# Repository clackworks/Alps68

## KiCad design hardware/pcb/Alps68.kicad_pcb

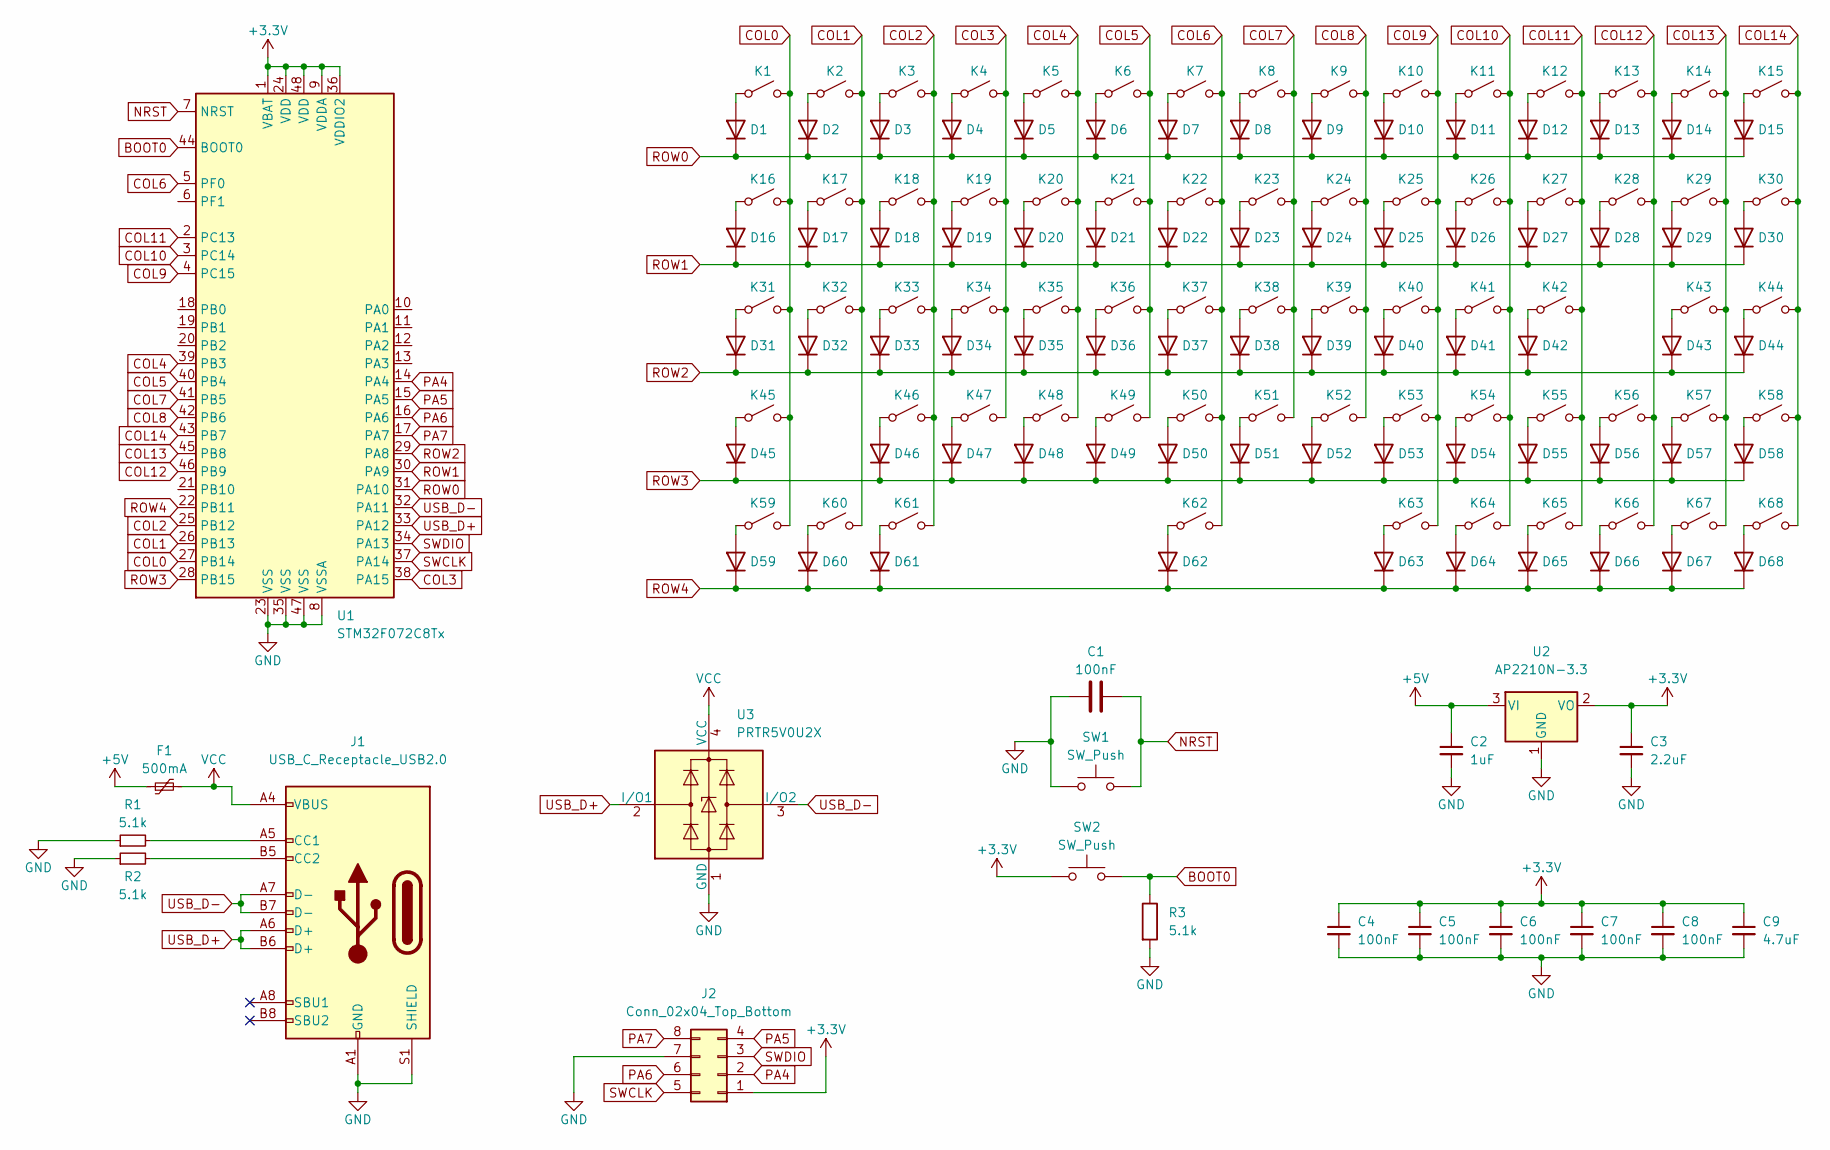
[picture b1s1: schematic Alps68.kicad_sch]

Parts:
C1, C4, C5, C6, C7, C8: 100nF; C_0805_2012Metric
C2: 1uF; C_0805_2012Metric
C3: 2.2uF; C_0805_2012Metric
C9: 4.7uF; C_0805_2012Metric
D1, D2, D3, D4, D5, D6, D7, D8, D9, D10, D11, D12, D13, D14, D15, D16, D17, D18, D19, D20, D21, D22, D23, D24, D25, D26, D27, D28, D29, D30, D31, D32, D33, D34, D35, D36, D37, D38, D39, D40, D41, D42, D43, D44, D45, D46, D47, D48, D49, D50, D51, D52, D53, D54, D55, D56, D57, D58, D59, D60, D61, D62, D63, D64, D65, D66, D67, D68: D; D_SOD-323_HandSoldering_NoSilkScreen
F1: 500mA; Fuse_0805_2012Metric
J1: USB_C_Receptacle_USB2.0; USB_C_Receptacle_HRO_TYPE-C-31-M-12
J2: Conn_02x04_Top_Bottom; PinHeader_2x04_P2.54mm_Vertical
K1, K2, K3, K4, K5, K6, K7, K8, K9, K10, K11, K12, K13, K15, K17, K18, K19, K20, K21, K22, K23, K24, K25, K26, K27, K28, K30, K32, K33, K34, K35, K36, K37, K38, K39, K40, K41, K42, K44, K46, K47, K48, K49, K50, K51, K52, K53, K54, K55, K57, K58, K63, K64, K65, K66, K67, K68: MX_Alps_Hybrid; MX-1U-NoLED
K14: MX_Alps_Hybrid; MX-2U-NoLED
K16, K29: MX_Alps_Hybrid; MX-1.5U-NoLED
K31, K56: MX_Alps_Hybrid; MX-1.75U-NoLED
K43, K45: MX_Alps_Hybrid; MX-2.25U-NoLED
K59, K60, K61: MX_Alps_Hybrid; MX-1.25U-NoLED
K62: MX_Alps_Hybrid; MX-6.25U-ReversedStabilizers-NoLED
R1, R2, R3: 5.1k; R_0805_2012Metric
SW1, SW2: SW_Push; SW_SPST_TS-1177
U1: STM32F072C8Tx; LQFP-48_7x7mm_P0.5mm
U2: AP2210N-3.3; SOT-23
U3: PRTR5V0U2X; SOT-143

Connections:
+3V3: C3.1, C4.1, C5.1, C6.1, C7.1, C8.1, C9.1, J2.1, SW2.1, U1.1 (VBAT), U1.9 (VDDA), U1.24 (VDD), U1.36 (VDDIO2), U1.48 (VDD), U2.2 (VO); also elsewhere on the board
+5V: C2.1, F1.1, U2.3 (VI)
BOOT0: R3.1, SW2.2, U1.44 (BOOT0); also elsewhere on the board
COL0: K1.1 (A), K16.1 (A), K31.1 (A), K45.1 (A), K59.1 (A), U1.27 (PB14)
COL1: K2.1 (A), K17.1 (A), K32.1 (A), K60.1 (A), U1.26 (PB13)
COL2: K3.1 (A), K18.1 (A), K33.1 (A), K46.1 (A), K61.1 (A), U1.25 (PB12)
COL3: K4.1 (A), K19.1 (A), K34.1 (A), K47.1 (A), U1.38 (PA15)
COL4: K5.1 (A), K20.1 (A), K35.1 (A), K48.1 (A), U1.39 (PB3)
COL5: K6.1 (A), K21.1 (A), K36.1 (A), K49.1 (A), U1.40 (PB4)
COL6: K7.1 (A), K22.1 (A), K37.1 (A), K50.1 (A), K62.1 (A), U1.5 (PF0)
COL7: K8.1 (A), K23.1 (A), K38.1 (A), K51.1 (A), U1.41 (PB5)
COL8: K9.1 (A), K24.1 (A), K39.1 (A), K52.1 (A), U1.42 (PB6)
COL9: K10.1 (A), K25.1 (A), K40.1 (A), K53.1 (A), K63.1 (A), U1.4 (PC15)
COL10: K11.1 (A), K26.1 (A), K41.1 (A), K54.1 (A), K64.1 (A), U1.3 (PC14)
COL11: K12.1 (A), K27.1 (A), K42.1 (A), K55.1 (A), K65.1 (A), U1.2 (PC13)
COL12: K13.1 (A), K28.1 (A), K56.1 (A), K66.1 (A), U1.46 (PB9)
COL13: K14.1 (A), K29.1 (A), K43.1 (A), K57.1 (A), K67.1 (A), U1.45 (PB8)
COL14: K15.1 (A), K30.1 (A), K44.1 (A), K58.1 (A), K68.1 (A), U1.43 (PB7)
GND: C1.1, C2.2, C3.2, C4.2, C5.2, C6.2, C7.2, C8.2, C9.2, J1.A1 (GND), J1.A12 (GND), J1.B1 (GND), J1.B12 (GND), J1.S1 (SHIELD), J2.7, R1.1, R2.1, R3.2, SW1.1, U1.8 (VSSA), U1.23 (VSS), U1.35 (VSS), U1.47 (VSS), U2.1 (GND), U3.1 (GND); also elsewhere on the board
NRST: C1.2, SW1.2, U1.7 (NRST); also elsewhere on the board
unnamed: D1.2 (A), K1.2 (B)
unnamed: D2.2 (A), K2.2 (B)
unnamed: D3.2 (A), K3.2 (B)
unnamed: D4.2 (A), K4.2 (B)
unnamed: D5.2 (A), K5.2 (B)
unnamed: D6.2 (A), K6.2 (B)
unnamed: D7.2 (A), K7.2 (B)
unnamed: D8.2 (A), K8.2 (B)
unnamed: D9.2 (A), K9.2 (B)
unnamed: D10.2 (A), K10.2 (B)
unnamed: D11.2 (A), K11.2 (B)
unnamed: D12.2 (A), K12.2 (B)
unnamed: D13.2 (A), K13.2 (B)
unnamed: D14.2 (A), K14.2 (B)
unnamed: D15.2 (A), K15.2 (B)
unnamed: D16.2 (A), K16.2 (B)
unnamed: D17.2 (A), K17.2 (B)
unnamed: D18.2 (A), K18.2 (B)
unnamed: D19.2 (A), K19.2 (B)
unnamed: D20.2 (A), K20.2 (B)
unnamed: D21.2 (A), K21.2 (B)
unnamed: D22.2 (A), K22.2 (B)
unnamed: D23.2 (A), K23.2 (B)
unnamed: D24.2 (A), K24.2 (B)
unnamed: D25.2 (A), K25.2 (B)
unnamed: D26.2 (A), K26.2 (B)
unnamed: D27.2 (A), K27.2 (B)
unnamed: D28.2 (A), K28.2 (B)
unnamed: D29.2 (A), K29.2 (B)
unnamed: D30.2 (A), K30.2 (B)
unnamed: D31.2 (A), K31.2 (B)
unnamed: D32.2 (A), K32.2 (B)
unnamed: D33.2 (A), K33.2 (B)
unnamed: D34.2 (A), K34.2 (B)
unnamed: D35.2 (A), K35.2 (B)
unnamed: D36.2 (A), K36.2 (B)
unnamed: D37.2 (A), K37.2 (B)
unnamed: D38.2 (A), K38.2 (B)
unnamed: D39.2 (A), K39.2 (B)
unnamed: D40.2 (A), K40.2 (B)
unnamed: D41.2 (A), K41.2 (B)
unnamed: D42.2 (A), K42.2 (B)
unnamed: D43.2 (A), K43.2 (B)
unnamed: D44.2 (A), K44.2 (B)
unnamed: D45.2 (A), K45.2 (B)
unnamed: D46.2 (A), K46.2 (B)
unnamed: D47.2 (A), K47.2 (B)
unnamed: D48.2 (A), K48.2 (B)
unnamed: D49.2 (A), K49.2 (B)
unnamed: D50.2 (A), K50.2 (B)
unnamed: D51.2 (A), K51.2 (B)
unnamed: D52.2 (A), K52.2 (B)
unnamed: D53.2 (A), K53.2 (B)
unnamed: D54.2 (A), K54.2 (B)
unnamed: D55.2 (A), K55.2 (B)
unnamed: D56.2 (A), K56.2 (B)
unnamed: D57.2 (A), K57.2 (B)
unnamed: D58.2 (A), K58.2 (B)
unnamed: D59.2 (A), K59.2 (B)
unnamed: D60.2 (A), K60.2 (B)
unnamed: D61.2 (A), K61.2 (B)
unnamed: D62.2 (A), K62.2 (B)
unnamed: D63.2 (A), K63.2 (B)
unnamed: D64.2 (A), K64.2 (B)
unnamed: D65.2 (A), K65.2 (B)
unnamed: D66.2 (A), K66.2 (B)
unnamed: D67.2 (A), K67.2 (B)
unnamed: D68.2 (A), K68.2 (B)
unnamed: J1.A5 (CC1), R1.2
unnamed: J1.B5 (CC2), R2.2
PA4: J2.2, U1.14 (PA4)
PA5: J2.4, U1.15 (PA5)
PA6: J2.6, U1.16 (PA6)
PA7: J2.8, U1.17 (PA7)
ROW0: D1.1 (K), D2.1 (K), D3.1 (K), D4.1 (K), D5.1 (K), D6.1 (K), D7.1 (K), D8.1 (K), D9.1 (K), D10.1 (K), D11.1 (K), D12.1 (K), D13.1 (K), D14.1 (K), D15.1 (K), U1.31 (PA10)
ROW1: D16.1 (K), D17.1 (K), D18.1 (K), D19.1 (K), D20.1 (K), D21.1 (K), D22.1 (K), D23.1 (K), D24.1 (K), D25.1 (K), D26.1 (K), D27.1 (K), D28.1 (K), D29.1 (K), D30.1 (K), U1.30 (PA9)
ROW2: D31.1 (K), D32.1 (K), D33.1 (K), D34.1 (K), D35.1 (K), D36.1 (K), D37.1 (K), D38.1 (K), D39.1 (K), D40.1 (K), D41.1 (K), D42.1 (K), D43.1 (K), D44.1 (K), U1.29 (PA8)
ROW3: D45.1 (K), D46.1 (K), D47.1 (K), D48.1 (K), D49.1 (K), D50.1 (K), D51.1 (K), D52.1 (K), D53.1 (K), D54.1 (K), D55.1 (K), D56.1 (K), D57.1 (K), D58.1 (K), U1.28 (PB15)
ROW4: D59.1 (K), D60.1 (K), D61.1 (K), D62.1 (K), D63.1 (K), D64.1 (K), D65.1 (K), D66.1 (K), D67.1 (K), D68.1 (K), U1.22 (PB11)
SWCLK: J2.5, U1.37 (PA14)
SWDIO: J2.3, U1.34 (PA13)
USB_D+: J1.A6 (D+), J1.B6 (D+), U1.33 (PA12), U3.2 (I/O1)
USB_D-: J1.A7 (D-), J1.B7 (D-), U1.32 (PA11), U3.3 (I/O2)
VCC: F1.2, J1.A4 (VBUS), J1.A9 (VBUS), J1.B4 (VBUS), J1.B9 (VBUS), U3.4 (VCC)

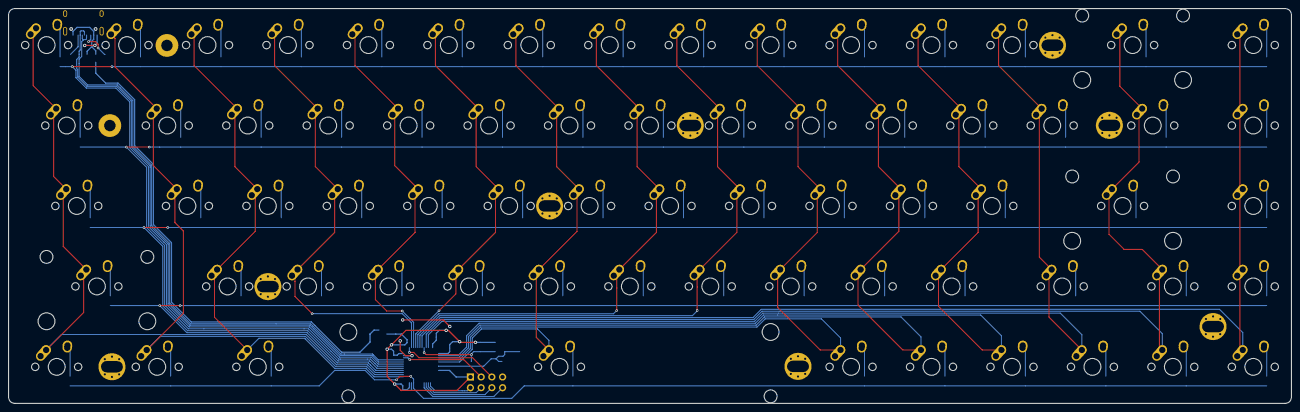
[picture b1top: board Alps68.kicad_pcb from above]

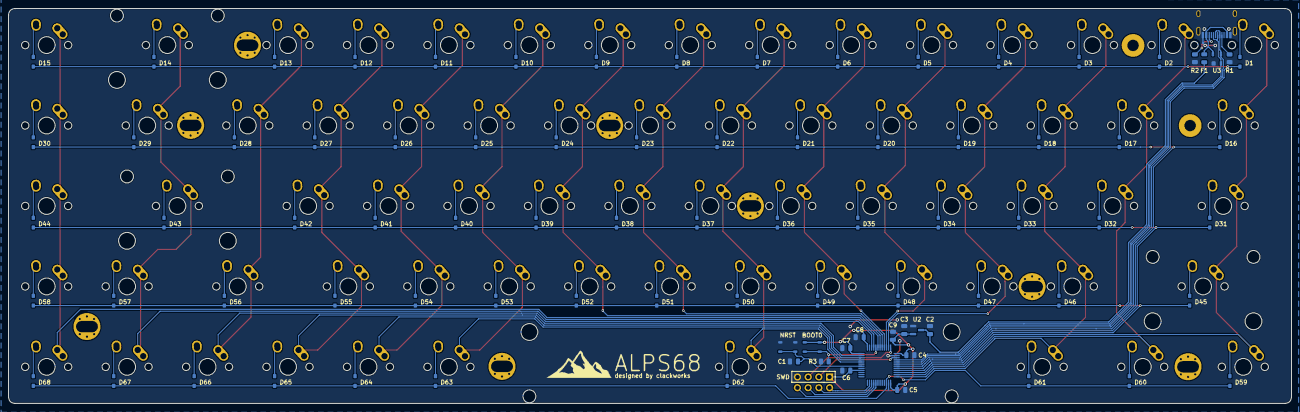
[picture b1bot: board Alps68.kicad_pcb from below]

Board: 2 copper layers, 303.8 x 93.5 mm, 156 parts (88 on the bottom side), 104 nets.

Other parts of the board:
BOOT0: SW_Push; SW_SPST_TS-1177
NRST: SW_Push; SW_SPST_TS-1177

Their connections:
+3V3: BOOT0.1; also elsewhere on the board
BOOT0: BOOT0.2; also elsewhere on the board
GND: NRST.1; also elsewhere on the board
NRST: NRST.2; also elsewhere on the board

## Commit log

2022-09-13 Add BOM for PCB
